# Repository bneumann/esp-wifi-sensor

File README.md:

# Temperature/Humidity Sensor SHT21 with ESP8266
There are a lot of IOT sensor projects out there. Why would I do my own one? First: Because I can and the fun it brings. Or frustration. Or a bit of both. Second, I was looking for a decent driver that actually works with the SHT21. None of the stock Adafruit libraries worked for me. And when I checked my logic analyzer all the drives had the same bug.
SO: I also wrote my own driver. Later on I ported it to the ESP-01 which only has 2 Pins available so I bit banged my own i2c driver too.
Maybe some people can learn from the code (sorry for the sparse comments), that's why I put it online. Feel free to ask questions!

I also provide my layout file which I use for the sensors in my house.

## Wifi credentials
Because I don't want you guys to spoof around my wifi, I didn't check in the credentials. Clever ey? So you will need to create your own `credentials.h` file in the base directory:
```c
#define WLAN_SSID       "YOURID"
#define WLAN_PASS       "YOURPW"
#define DEVICE_NAME     "bathroom"
#define AIO_SERVER      "servername"
#define AIO_SERVERPORT  1883
```

## I2C driver
As I said, that one is simple bit banging the basic start, stop, read and write methods. Check the header file `i2c.h` for available methods. Might be a cool starting point if you want your own sensor or peripheral and only have 2 pins.

## SHT21 driver
On top of the i2c driver sits the SHT21 driver using the no hold measurement. Which basically means, that I am polling the lil fella until he's done measuring.
All my SHT21s I have didn't work with the Adafruit driver which uses the hold measurement. They pull down the clock line until the SHT21 is done measuring and continue from there. 
The driver contains of a few basic steps:
```c
// Create a callback method
void measurementDoneCb(const uint16_t *temp, const  uint16_t *humid)
{
  if (*temp && *humid) {
    // do what you want with the data
  }
}
/* .... other code .... */
// initialise SHT
sht_init(); // takes about 15ms
// Trigger a measurement
sht_trigger_measurement(TRG_TEMP_MEAS_NO_HOLD, measurementDoneCb);
// Trigger another one. You could do that in the callback if you want too
sht_trigger_measurement(TRG_HUMI_MEAS_NO_HOLD, measurementDoneCb);
```

### Sensor data conversion
The data from the sensor is some digital data. You need to calculate it using these formulas. I conveniently put them into C code already:
```c
float calculateTemperature(uint16_t temp) {
  return -46.85 + 175.72 * ((float)temp) / 65536.0;
}

float calculateHumidity(uint16_t temp) {
  return -6.0 + 125.0 * ((float)temp) / 65536.0;
}
```

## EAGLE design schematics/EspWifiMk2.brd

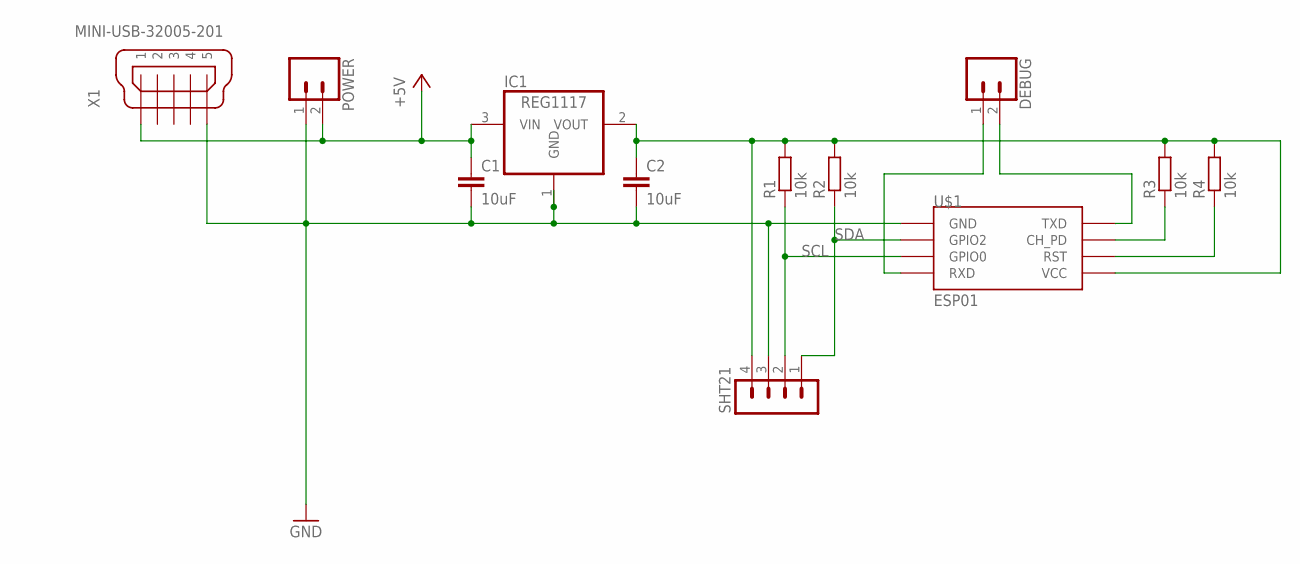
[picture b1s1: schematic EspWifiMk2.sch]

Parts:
C1, C2: 10uF; C1206
DEBUG: CONN_02; 1X02
IC1: REG1117; SOT223
POWER: CONN_02; 1X02
R1, R2, R3, R4: 10k; M1206
SHT21: MA04-1
U$1: ESP01
X1: MINI-USB-32005-201; 32005-201

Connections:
3V3: C2.1, IC1.2 (VOUT), R1.2, R2.2, R3.2, R4.2, SHT21.4, U$1.VCC
+5V: C1.1, IC1.3 (VIN), POWER.2, X1.1
GND: C1.2, C2.2, IC1.1 (GND), POWER.1, SHT21.3, U$1.GND, X1.5
unnamed: R3.1, U$1.CH_PD
unnamed: R4.1, U$1.RST
unnamed: DEBUG.1, U$1.RX (RXD)
unnamed: DEBUG.2, U$1.TX (TXD)
SCL: R1.1, SHT21.2, U$1.GPIO0
SDA: R2.1, SHT21.1, U$1.GPIO2

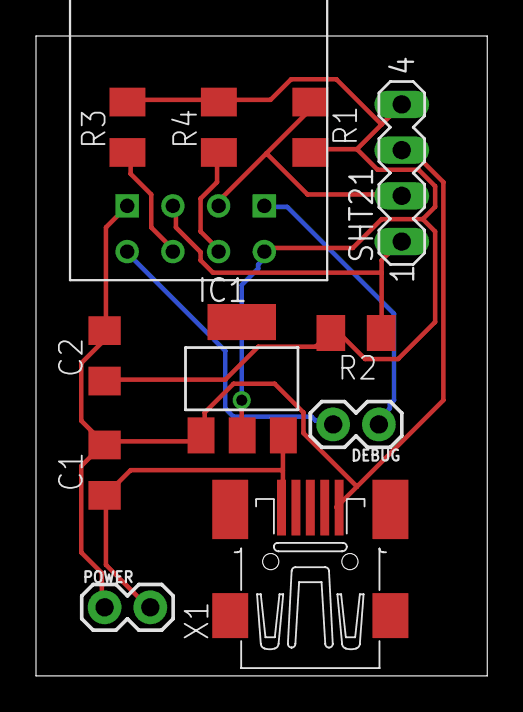
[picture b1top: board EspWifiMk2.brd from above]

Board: 2 copper layers, 25.1 x 35.5 mm, 12 parts (0 on the bottom side), 9 nets.

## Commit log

2018-03-05 Added basic README and fixed define
2018-03-05 Filled readme, cosmetics
2018-03-05 cosmetics
2018-03-05 Finished readme
2018-03-05 Fixed drawings in i2c
2019-04-16 Added debugging information in case of Development switch
2019-04-16 Reenabled correct measured data
2020-03-03 improved power saving

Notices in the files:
parts and their libraries:
SparkFun-Retired: Licensing: Creative Commons ShareAlike 4.0 International - https://creativecommons.org/licenses/by-sa/4.0
